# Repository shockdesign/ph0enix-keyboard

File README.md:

# ph0enix-keyboard

A 40% keyboard consisting of 44 keys.

My attempt of minimising a keyboard but keeping the ability to have some
dedicated arrow keys.

Firmware is currently for KMK as the board is setup to be able to solder a
Raspberry Pi Pico to it.

### Parts

| Quantity | Part name            | Link                                                     |
|----------|----------------------|----------------------------------------------------------|
| 1        | ph0enix PCB          |                                                          |
| 44       | SMA Diodes           | https://www.lcsc.com/product-detail/_Yint-_C2920036.html |
| 1        | Raspberry Pi Pico    |                                                          |
| 1        | Micro USB cable      |                                                          |
| 44       | MX style switches    |                                                          |
| 1        | 40 pin male header   |                                                          |
| 1        | 40 pin female header | (optional)                                               |

License in play is CERN-OHL-W-2.0.

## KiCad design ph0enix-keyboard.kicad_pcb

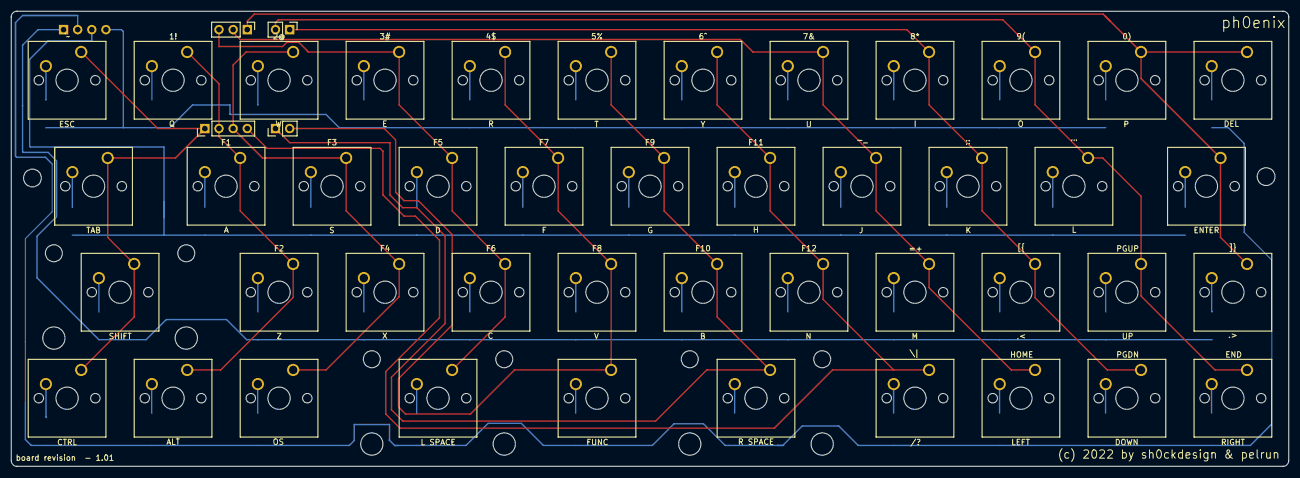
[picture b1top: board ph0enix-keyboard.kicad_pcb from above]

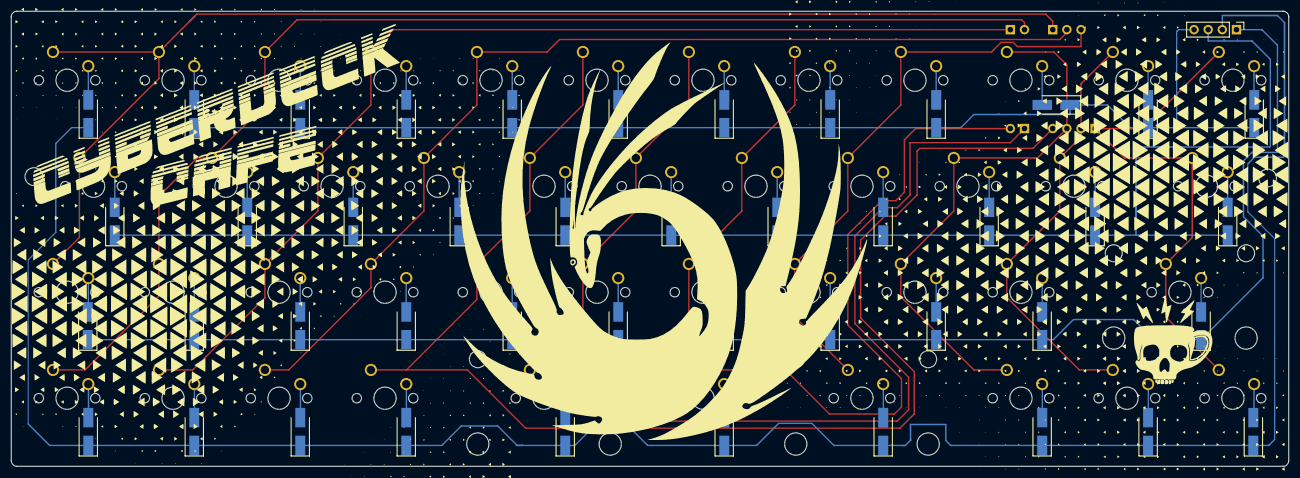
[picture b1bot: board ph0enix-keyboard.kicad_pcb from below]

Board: 2 copper layers, 229.6 x 81.8 mm, 90 parts (44 on the bottom side), 59 nets.

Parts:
0), 1!, 2@, 3#, 4$, 5%, 6^, 7&, 8*, 9(: KEYSW; SW_Cherry_MX_1.00u_PCB
ALT: KEYSW; SW_Cherry_MX_1.00u_PCB
CTRL: KEYSW; SW_Cherry_MX_1.00u_PCB
D1, D2, D3, D4, D5, D6, D7, D8, D9, D10, D11, D12, D13, D14, D15, D16, D17, D18, D19, D20, D21, D22, D23, D24, D25, D26, D27, D28, D29, D30, D31, D32, D33, D35, D36, D37, D38, D39, D40, D41, D42, D43: D; D_SMA_Handsoldering
DEL: KEYSW; SW_Cherry_MX_1.00u_PCB
DOWN: KEYSW; SW_Cherry_MX_1.00u_PCB
ENTER: KEYSW; SW_Cherry_MX_1.50u_PCB
F1, F2, F3, F4, F5, F6, F7, F8, F9, F10, F11, F12: KEYSW; SW_Cherry_MX_1.00u_PCB
FUNC: KEYSW; SW_Cherry_MX_1.00u_PCB
H1, H2: MountingHole; MountingHole_3.2mm_M3_DIN965
J: KEYSW; SW_Cherry_MX_1.00u_PCB
K: KEYSW; SW_Cherry_MX_1.00u_PCB
L: KEYSW; SW_Cherry_MX_1.00u_PCB
L SPACE: KEYSW; SW_Cherry_MX_2.00u_PCB
LEFT: KEYSW; SW_Cherry_MX_1.00u_PCB
M: KEYSW; SW_Cherry_MX_1.00u_PCB
OS: KEYSW; SW_Cherry_MX_1.00u_PCB
R SPACE: KEYSW; SW_Cherry_MX_2.00u_PCB
RIGHT: KEYSW; SW_Cherry_MX_1.00u_PCB
SHIFT: KEYSW; SW_Cherry_MX_2.00u_PCB
TAB: KEYSW; SW_Cherry_MX_1.50u_PCB
UP: KEYSW; SW_Cherry_MX_1.00u_PCB
[{: KEYSW; SW_Cherry_MX_1.00u_PCB
\|: KEYSW; SW_Cherry_MX_1.00u_PCB
]}: KEYSW; SW_Cherry_MX_1.00u_PCB
`~: KEYSW; SW_Cherry_MX_1.00u_PCB
locked: D; D_SMA_Handsoldering
locked#2: D; D_SMA_Handsoldering

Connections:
/Col_0: CTRL.1, SHIFT.1, TAB.1, `~.1
/Col_1: 1!.1, ALT.1, F1.1, F2.1
/Col_2: 2@.1, F3.1, F4.1, OS.1
/Col_3: 3#.1, F5.1, F6.1, L SPACE.1
/Col_4: 4$.1, F7.1, F8.1, FUNC.1
/Col_5: 5%.1, F9.1, F10.1, R SPACE.1
/Col_6: 6^.1, F11.1, F12.1, \|.1
/Col_7: 7&.1, J.1, LEFT.1, M.1
/Col_8: 8*.1, DOWN.1, K.1, [{.1
/Col_9: 9(.1, L.1, RIGHT.1, UP.1
/Col_10: 0).1, DEL.1, ENTER.1, ]}.1
/Row_0: D1.1 (K), D2.1 (K), D3.1 (K), D4.1 (K), D5.1 (K), D6.1 (K), D7.1 (K), D8.1 (K), D9.1 (K), D10.1 (K), locked.1 (K)
/Row_1: D12.1 (K), D13.1 (K), D14.1 (K), D15.1 (K), D16.1 (K), D17.1 (K), D18.1 (K), D19.1 (K), D20.1 (K), D21.1 (K), D22.1 (K)
/Row_2: D23.1 (K), D24.1 (K), D25.1 (K), D26.1 (K), D27.1 (K), D28.1 (K), D29.1 (K), D30.1 (K), D31.1 (K), D32.1 (K), D33.1 (K)
/Row_3: D11.1 (K), D35.1 (K), D36.1 (K), D37.1 (K), D38.1 (K), D39.1 (K), D40.1 (K), D41.1 (K), D42.1 (K), D43.1 (K), locked#2.1 (K)
unnamed: `~.2, locked.2 (A)
unnamed: 1!.2, D1.2 (A)
unnamed: 2@.2, D2.2 (A)
unnamed: 3#.2, D3.2 (A)
unnamed: 4$.2, D4.2 (A)
unnamed: 5%.2, D5.2 (A)
unnamed: 6^.2, D6.2 (A)
unnamed: 7&.2, D7.2 (A)
unnamed: 8*.2, D8.2 (A)
unnamed: 9(.2, D9.2 (A)
unnamed: 0).2, D10.2 (A)
unnamed: D11.2 (A), DEL.2
unnamed: D12.2 (A), TAB.2
unnamed: D13.2 (A), F1.2
unnamed: D14.2 (A), F3.2
unnamed: D15.2 (A), F5.2
unnamed: D16.2 (A), F7.2
unnamed: D17.2 (A), F9.2
unnamed: D18.2 (A), F11.2
unnamed: D19.2 (A), J.2
unnamed: D20.2 (A), K.2
unnamed: D21.2 (A), L.2
unnamed: D22.2 (A), ENTER.2
unnamed: D23.2 (A), SHIFT.2
unnamed: D24.2 (A), F2.2
unnamed: D25.2 (A), F4.2
unnamed: D26.2 (A), F6.2
unnamed: D27.2 (A), F8.2
unnamed: D28.2 (A), F10.2
unnamed: D29.2 (A), F12.2
unnamed: D30.2 (A), M.2
unnamed: D31.2 (A), [{.2
unnamed: D32.2 (A), UP.2
unnamed: D33.2 (A), ]}.2
unnamed: CTRL.2, locked#2.2 (A)
unnamed: ALT.2, D35.2 (A)
unnamed: D36.2 (A), OS.2
unnamed: D37.2 (A), L SPACE.2
unnamed: D38.2 (A), FUNC.2
unnamed: D39.2 (A), R SPACE.2
unnamed: D40.2 (A), \|.2
unnamed: D41.2 (A), LEFT.2
unnamed: D42.2 (A), DOWN.2
unnamed: D43.2 (A), RIGHT.2

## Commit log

2022-07-29 Commit of board, revision 1.01 ready for production
2022-08-05 Added an image of the keyboard layout
2022-08-08 Updated with cyberdeck cafe logo
2022-08-10 Updated imagery
2022-08-10 And updated again
2023-03-02 Updated parts list
2023-05-15 Added sample boot.py

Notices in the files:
ph0enix-keyboard.kicad_pcb:
(c) 2022 by sh0ckdesign & pelrun
